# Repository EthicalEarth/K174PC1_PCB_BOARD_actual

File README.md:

# K174PC1_PCB_BOARD_actual
An UKW (Ultra Short Waves) converter (165MHz -> 120Mhz), Kicad project. CHIP: К174ПС1

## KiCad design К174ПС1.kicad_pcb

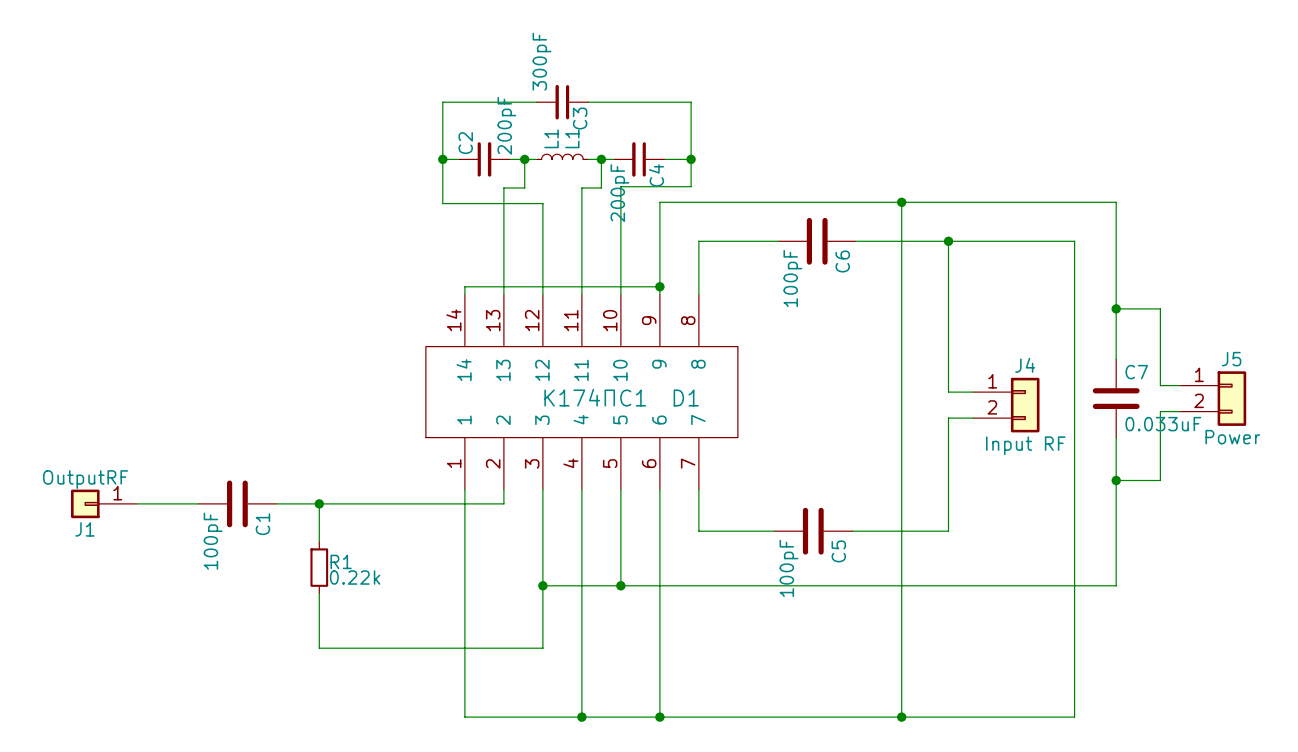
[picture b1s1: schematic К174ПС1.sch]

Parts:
C1, C5, C6: 100pF; C_Disc_D4.3mm_W1.9mm_P5.00mm
C2, C4: 200pF; C_Disc_D4.3mm_W1.9mm_P5.00mm
C3: 300pF; C_Disc_D7.5mm_W5.0mm_P7.50mm
C7: 0.033uF; C_Disc_D4.3mm_W1.9mm_P5.00mm
D1: К174ПС1; DIP-14_W7.62mm_LongPads
J1: OutputRF; Pin_Header_Straight_1x01_Pitch2.54mm
J4: Input RF; Pin_Header_Straight_1x02_Pitch2.54mm
J5: Power; Pin_Header_Straight_1x02_Pitch2.54mm
L1: L1; L_Axial_L6.6mm_D2.7mm_P10.16mm_Horizontal_Vishay_IM-2
R1: 0.22k; R_Axial_DIN0204_L3.6mm_D1.6mm_P7.62mm_Horizontal

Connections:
unnamed: C1.1, D1.2, R1.1
unnamed: C1.2, J1.1
unnamed: C2.1, C3.2, D1.12
unnamed: C2.2, D1.13, L1.1
unnamed: C3.1, C4.1, D1.10
unnamed: C4.2, D1.11, L1.2
unnamed: C5.1, J4.2
unnamed: C5.2, D1.7
unnamed: C6.1, C7.1, D1.1, D1.4, D1.6, D1.9, D1.14, J4.1, J5.1
unnamed: C6.2, D1.8
unnamed: C7.2, D1.3, D1.5, J5.2, R1.2

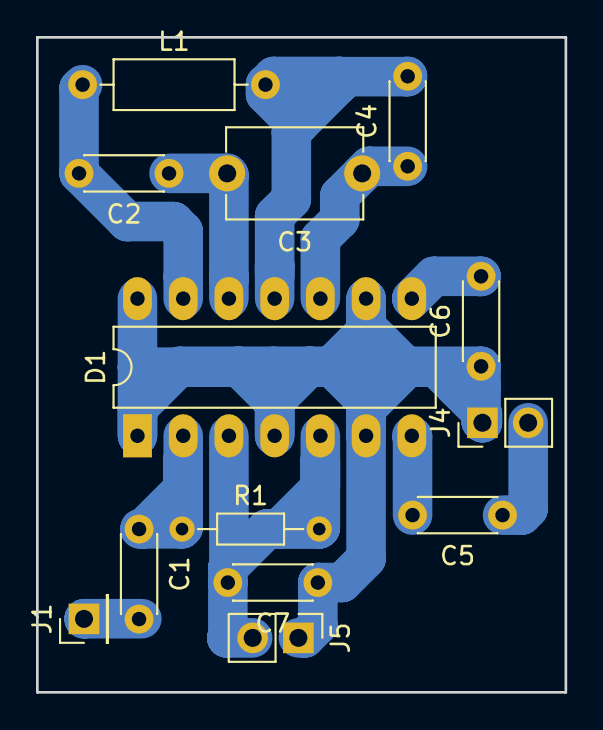
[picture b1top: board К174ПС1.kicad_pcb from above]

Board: 2 copper layers, 29.4 x 36.4 mm, 13 parts (0 on the bottom side), 11 nets.

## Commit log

2018-07-28 Init
